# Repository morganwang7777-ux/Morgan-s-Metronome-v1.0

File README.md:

# Morgan's Metronome v1.0

Arduino-based digital metronome developed from a breadboard prototype into a custom KiCad PCB shield. (First Project)
I built this project to learn how to use Arduino hardware and software and to create a working metronome instead of having to purchase one to practice my sax.

## Features

- 100 mm × 90 mm size shield
- Adjustable 40–180 BPM
- 5 BPM increments using a 10k potentiometer
- Start/Stop button
- 2–7 beat pattern selection
- Accented first beat
- 16x2 LCD display
- LED beat indicator
- Passive buzzer
- Custom 2-layer Arduino Uno shield PCB

## Development

The project started as a simple buzzer and LED metronome.

I originally used `delay()` for timing, but testing against a reference metronome showed that the BPM was inaccurate. I replaced this with `millis()`-based timing so the beat interval could be tracked more reliably.

I also replaced button-based BPM control with a potentiometer. Since the analog input was too sensitive, I rounded the BPM to 5 BPM increments.

After finishing the breadboard prototype
- I recreated the circuit in KiCad
- Ran ERC/DRC checks
- Selected and measured component footprints
- Routed the PCB, added a bottom GND plane
- Generated Gerber files 

## Hardware

- Arduino Uno
- 16x2 LCD
- 10k potentiometer
- Passive buzzer
- 5mm LED
- 220Ω resistor
- 2 pushbuttons

## Future Improvements
Tap tempo
More rhythm modes
Standalone PCB without the Arduino Uno
Enclosure
Improved buzzer volume control

## Repository

```text
firmware/   Arduino code
hardware/   KiCad schematic and PCB
gerbers/    Manufacturing files
images/     Project screenshots

Version

Morgan's Metronome v1.0

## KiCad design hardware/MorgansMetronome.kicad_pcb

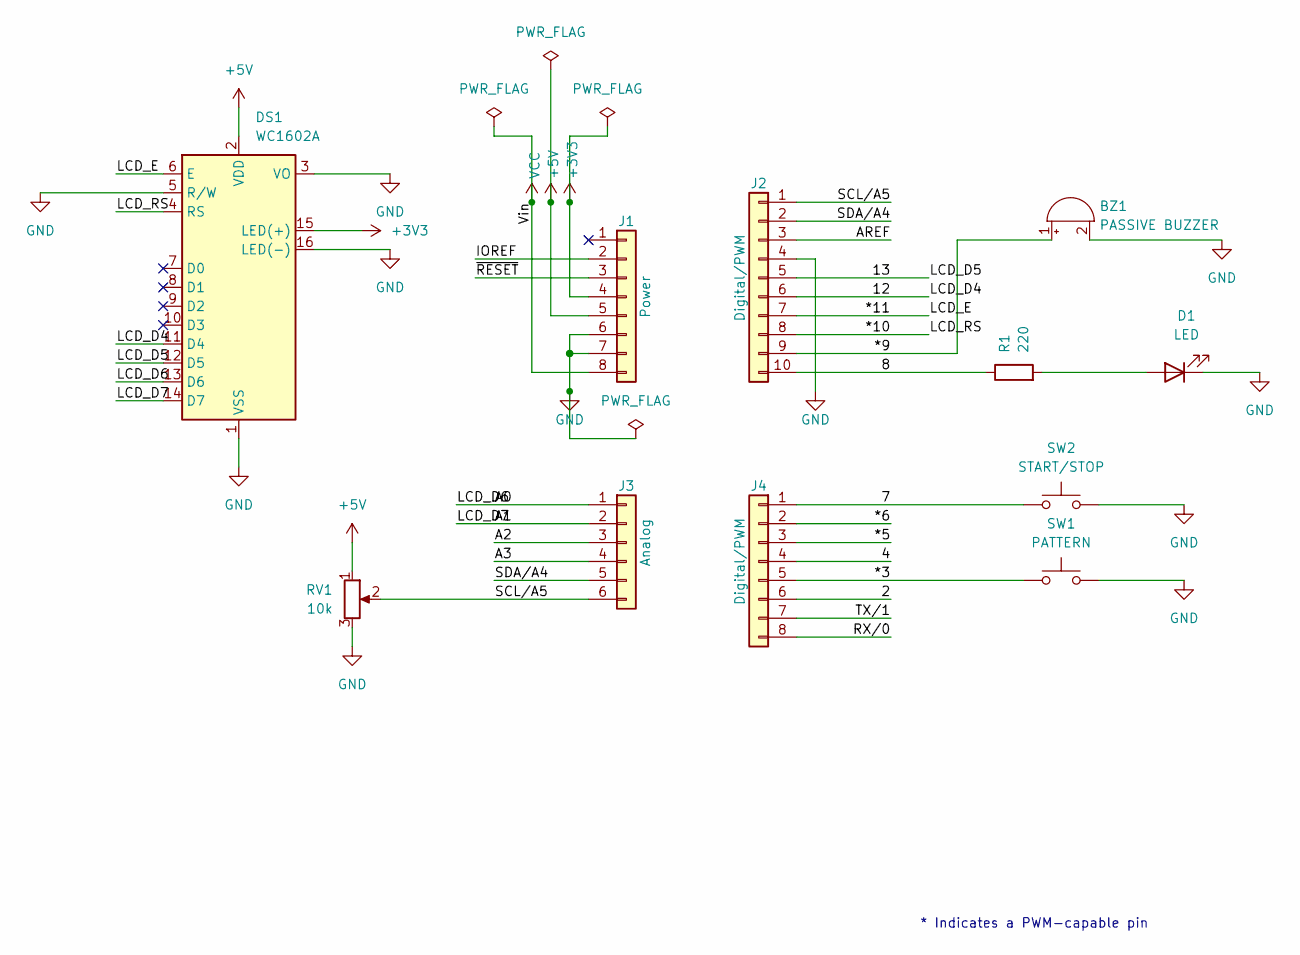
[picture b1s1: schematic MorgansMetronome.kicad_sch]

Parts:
BZ1: PASSIVE BUZZER; Buzzer_12x9.5RM7.6
D1: LED; LED_D5.0mm
DS1: WC1602A
J1: Power; PinHeader_1x08_P2.54mm_Vertical
J2: Digital/PWM; PinHeader_1x10_P2.54mm_Vertical
J3: Analog; PinHeader_1x06_P2.54mm_Vertical
J4: Digital/PWM; PinHeader_1x08_P2.54mm_Vertical
R1: 220; R_Axial_DIN0207_L6.3mm_D2.5mm_P10.16mm_Horizontal
RV1: 10k; Potentiometer_Alps_RK163_Single_Horizontal
SW1: PATTERN; SW_PUSH_6mm_H4.3mm
SW2: START/STOP; SW_PUSH_6mm_H4.3mm

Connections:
+3V3: DS1.15 (LED(+)), J1.4
+5V: DS1.2 (VDD), J1.5, RV1.1
/2: J4.6
/4: J4.4
/7: J4.1, SW2.1
/8: J2.10, R1.1
/12: DS1.11 (D4), J2.6
/13: DS1.12 (D5), J2.5
/*3: J4.5, SW1.1
/*5: J4.3
/*6: J4.2
/*9: BZ1.1 (+), J2.9
/*10: DS1.4 (RS), J2.8
/*11: DS1.6 (E), J2.7
/A0: DS1.13 (D6), J3.1
/A1: DS1.14 (D7), J3.2
/A2: J3.3
/A3: J3.4
/AREF: J2.3
/IOREF: J1.2
/RX/0: J4.8
/SCL/A5: J2.1, J3.6, RV1.2
/SDA/A4: J2.2, J3.5
/TX/1: J4.7
/~RESET: J1.3
GND: BZ1.2 (-), D1.1 (K), DS1.1 (VSS), DS1.3 (VO), DS1.5 (R/W), DS1.16 (LED(-)), J1.6, J1.7, J2.4, RV1.3, SW1.2, SW2.2
unnamed: D1.2 (A), R1.2
VCC: J1.8

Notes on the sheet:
* Indicates a PWM-capable pin

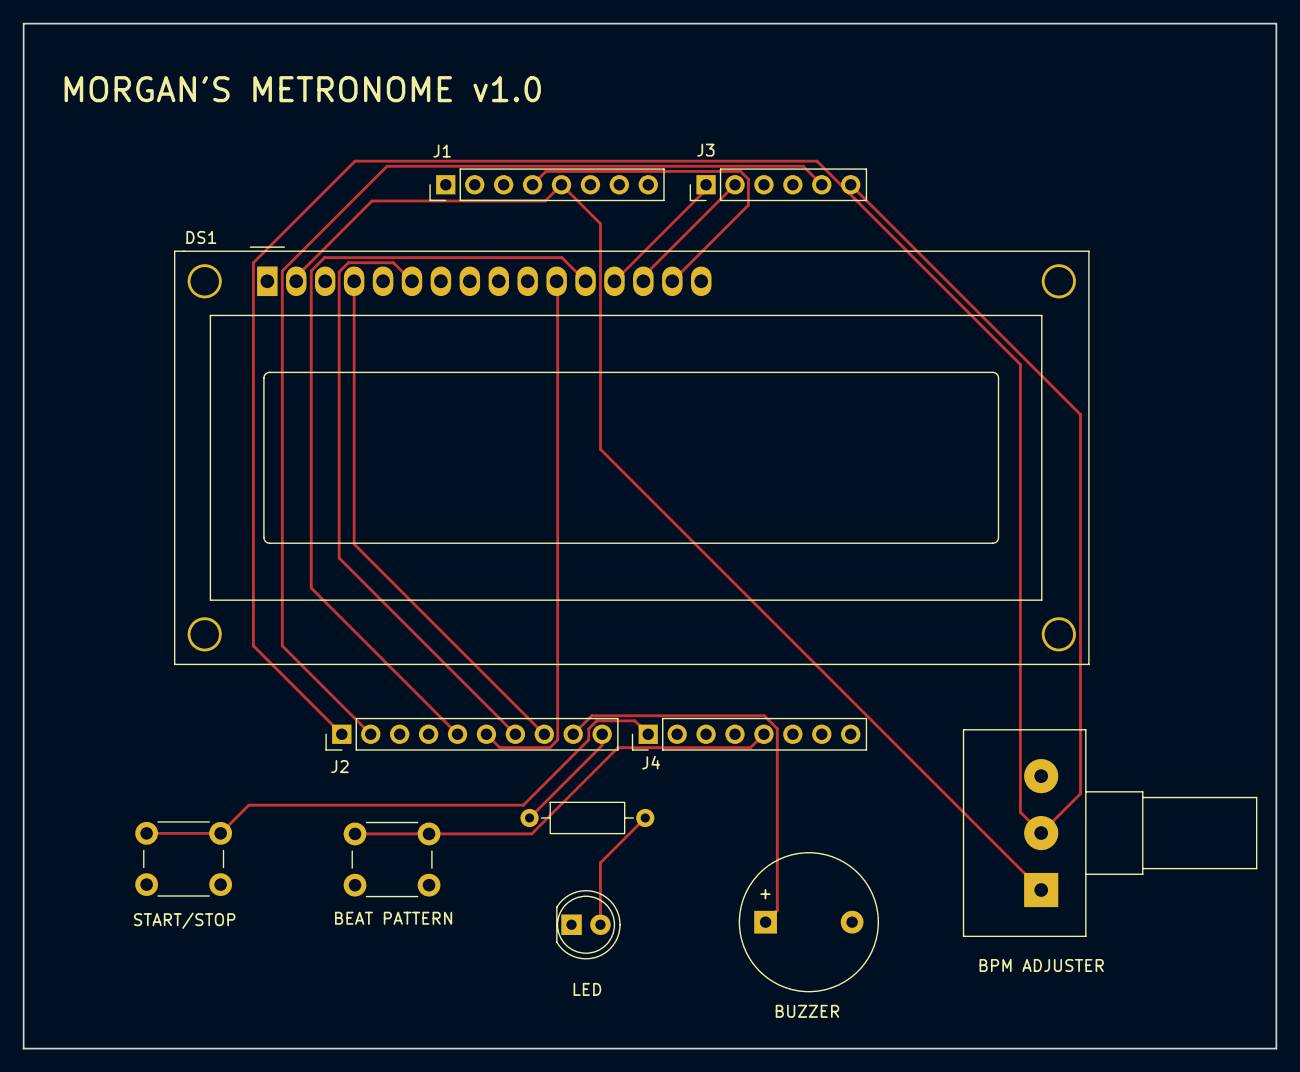
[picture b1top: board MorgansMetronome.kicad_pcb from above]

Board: 2 copper layers, 110.0 x 90.0 mm, 11 parts (0 on the bottom side), 16 nets.
